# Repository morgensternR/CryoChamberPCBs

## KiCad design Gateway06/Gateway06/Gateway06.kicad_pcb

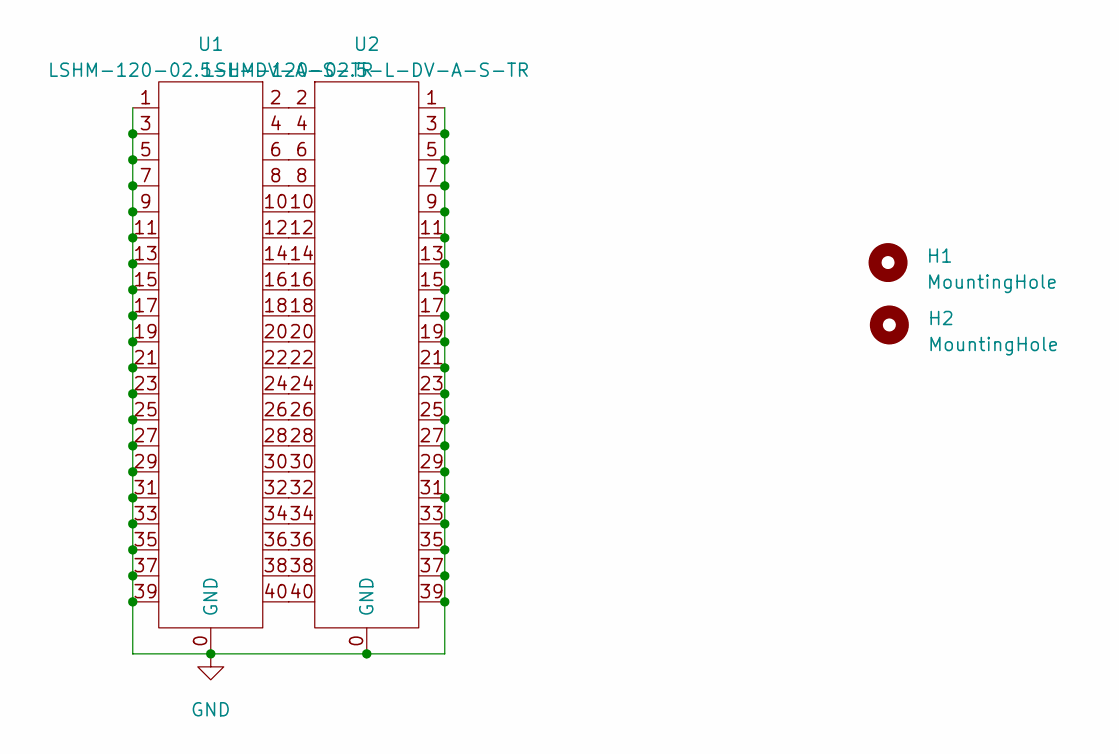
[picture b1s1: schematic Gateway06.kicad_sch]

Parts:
H1, H2: MountingHole; SMA_Hermetic
U1, U2: LSHM-120-02.5-L-DV-A-S-TR

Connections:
GND: U1.0 (GND), U1.1, U1.3, U1.5, U1.7, U1.9, U1.11, U1.13, U1.15, U1.17, U1.19, U1.21, U1.23, U1.25, U1.27, U1.29, U1.31, U1.33, U1.35, U1.37, U1.39, U2.0 (GND), U2.1, U2.3, U2.5, U2.7, U2.9, U2.11, U2.13, U2.15, U2.17, U2.19, U2.21, U2.23, U2.25, U2.27, U2.29, U2.31, U2.33, U2.35, U2.37, U2.39
unnamed: U1.2, U2.2
unnamed: U1.4, U2.4
unnamed: U1.6, U2.6
unnamed: U1.8, U2.8
unnamed: U1.10, U2.10
unnamed: U1.12, U2.12
unnamed: U1.14, U2.14
unnamed: U1.16, U2.16
unnamed: U1.18, U2.18
unnamed: U1.20, U2.20
unnamed: U1.22, U2.22
unnamed: U1.24, U2.24
unnamed: U1.26, U2.26
unnamed: U1.28, U2.28
unnamed: U1.30, U2.30
unnamed: U1.32, U2.32
unnamed: U1.34, U2.34
unnamed: U1.36, U2.36
unnamed: U1.38, U2.38
unnamed: U1.40, U2.40

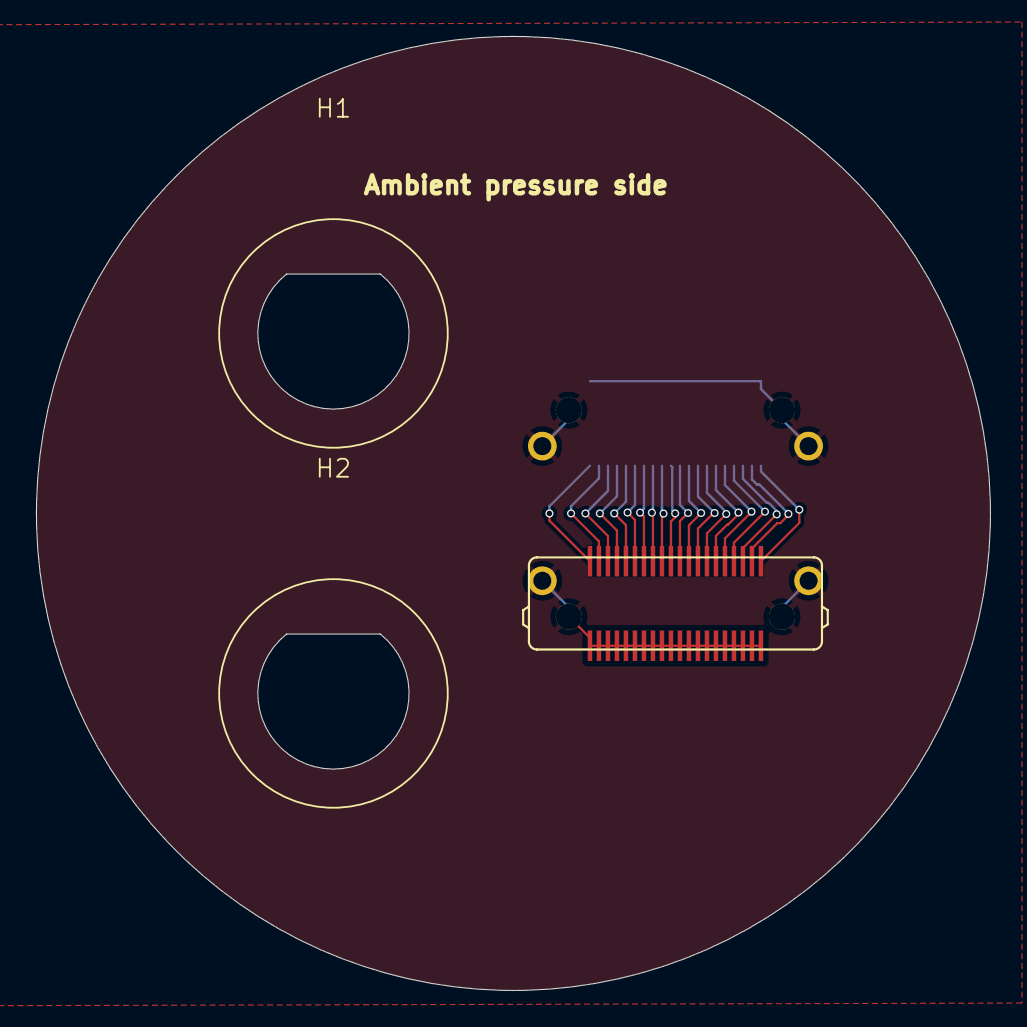
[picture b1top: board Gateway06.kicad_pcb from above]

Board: 2 copper layers, 53.0 x 53.0 mm, 4 parts (1 on the bottom side), 21 nets.

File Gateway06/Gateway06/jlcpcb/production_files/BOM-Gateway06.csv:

Comment,Designator,Footprint,LCSC
MountingHole,H2,SMA_Hermetic,
MountingHole,H1,SMA_Hermetic,
LSHM-120-02.5-L-DV-A-S-TR,U2,LSHM-120-02.5-L-DV-A-S-TR,
LSHM-120-02.5-L-DV-A-S-TR,U1,LSHM-120-02.5-L-DV-A-S-TR,

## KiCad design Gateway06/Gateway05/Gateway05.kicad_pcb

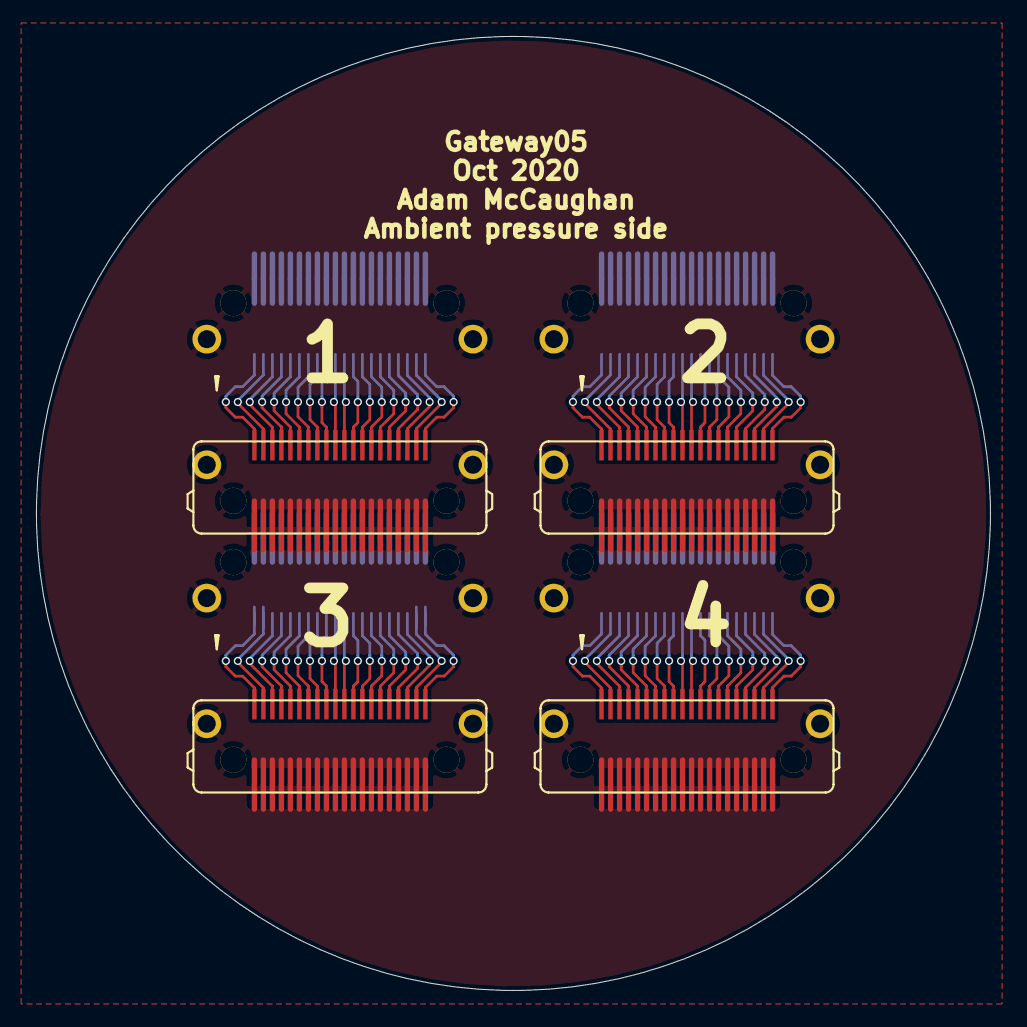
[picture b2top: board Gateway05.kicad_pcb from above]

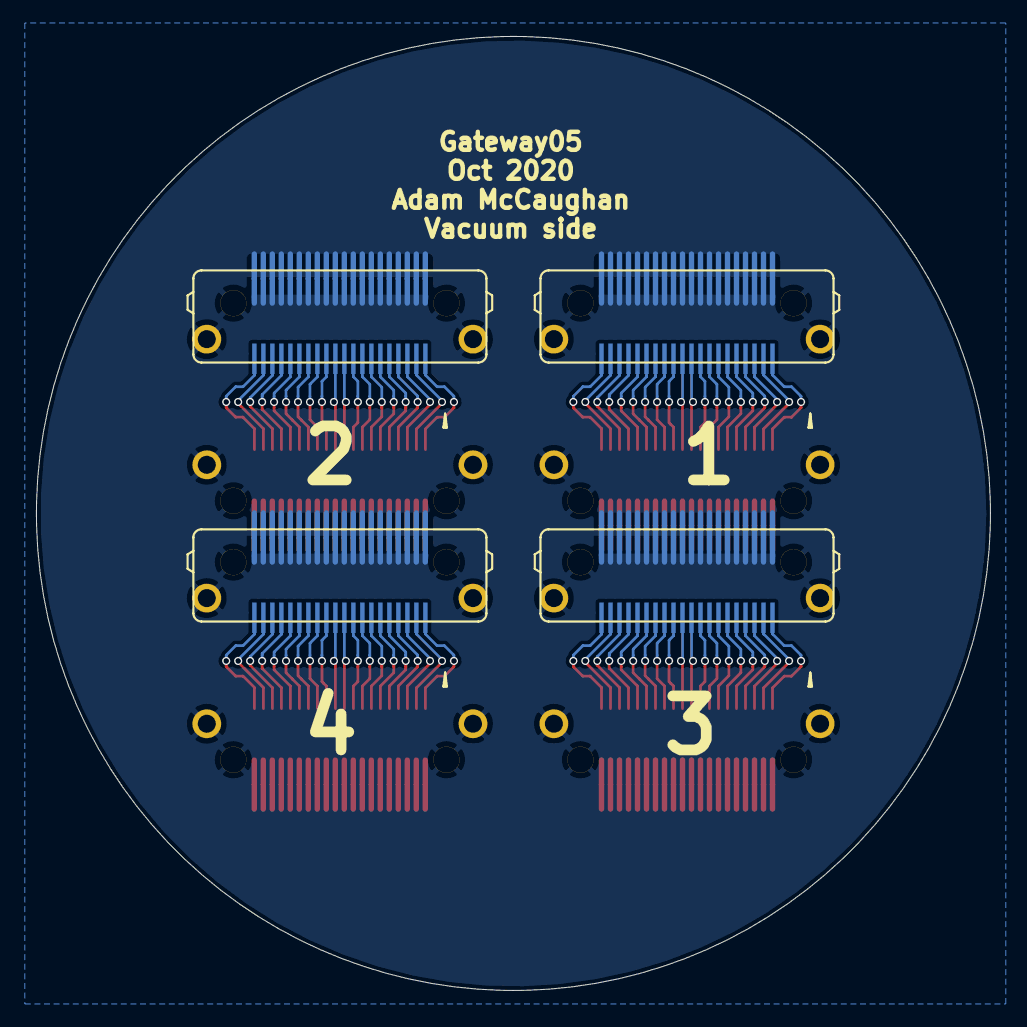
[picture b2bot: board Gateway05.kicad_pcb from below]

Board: 2 copper layers, 53.0 x 53.0 mm, 8 parts (4 on the bottom side), 81 nets.

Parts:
U1, U2, U3, U4, U5, U6, U7, U8: LSHM; LSHM-120-02.5-L-DV-A-S-TR

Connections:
GND: U1.0, U1.1, U1.3, U1.5, U1.7, U1.9, U1.11, U1.13, U1.15, U1.17, U1.19, U1.21, U1.23, U1.25, U1.27, U1.29, U1.31, U1.33, U1.35, U1.37, U1.39, U2.0, U2.1, U2.3, U2.5, U2.7, U2.9, U2.11, U2.13, U2.15, U2.17, U2.19, U2.21, U2.23, U2.25, U2.27, U2.29, U2.31, U2.33, U2.35, U2.37, U2.39, U3.0, U3.1, U3.3, U3.5, U3.7, U3.9, U3.11, U3.13, U3.15, U3.17, U3.19, U3.21, U3.23, U3.25, U3.27, U3.29, U3.31, U3.33, U3.35, U3.37, U3.39, U4.0, U4.1, U4.3, U4.5, U4.7, U4.9, U4.11, U4.13, U4.15, U4.17, U4.19, U4.21, U4.23, U4.25, U4.27, U4.29, U4.31, U4.33, U4.35, U4.37, U4.39, U5.0, U5.1, U5.3, U5.5, U5.7, U5.9, U5.11, U5.13, U5.15, U5.17, U5.19, U5.21, U5.23, U5.25, U5.27, U5.29, U5.31, U5.33, U5.35, U5.37, U5.39, U6.0, U6.1, U6.3, U6.5, U6.7, U6.9, U6.11, U6.13, U6.15, U6.17, U6.19, U6.21, U6.23, U6.25, U6.27, U6.29, U6.31, U6.33, U6.35, U6.37, U6.39, U7.0, U7.1, U7.3, U7.5, U7.7, U7.9, U7.11, U7.13, U7.15, U7.17, U7.19, U7.21, U7.23, U7.25, U7.27, U7.29, U7.31, U7.33, U7.35, U7.37, U7.39, U8.0, U8.1, U8.3, U8.5, U8.7, U8.9, U8.11, U8.13, U8.15, U8.17, U8.19, U8.21, U8.23, U8.25, U8.27, U8.29, U8.31, U8.33, U8.35, U8.37, U8.39
unnamed: U1.2, U2.2
unnamed: U1.4, U2.4
unnamed: U1.6, U2.6
unnamed: U1.8, U2.8
unnamed: U1.10, U2.10
unnamed: U1.12, U2.12
unnamed: U1.14, U2.14
unnamed: U1.16, U2.16
unnamed: U1.18, U2.18
unnamed: U1.20, U2.20
unnamed: U1.22, U2.22
unnamed: U1.24, U2.24
unnamed: U1.26, U2.26
unnamed: U1.28, U2.28
unnamed: U1.30, U2.30
unnamed: U1.32, U2.32
unnamed: U1.34, U2.34
unnamed: U1.36, U2.36
unnamed: U1.38, U2.38
unnamed: U1.40, U2.40
unnamed: U3.2, U4.2
unnamed: U3.4, U4.4
unnamed: U3.6, U4.6
unnamed: U3.8, U4.8
unnamed: U3.10, U4.10
unnamed: U3.12, U4.12
unnamed: U3.14, U4.14
unnamed: U3.16, U4.16
unnamed: U3.18, U4.18
unnamed: U3.20, U4.20
unnamed: U3.22, U4.22
unnamed: U3.24, U4.24
unnamed: U3.26, U4.26
unnamed: U3.28, U4.28
unnamed: U3.30, U4.30
unnamed: U3.32, U4.32
unnamed: U3.34, U4.34
unnamed: U3.36, U4.36
unnamed: U3.38, U4.38
unnamed: U3.40, U4.40
unnamed: U5.2, U6.2
unnamed: U5.4, U6.4
unnamed: U5.6, U6.6
unnamed: U5.8, U6.8
unnamed: U5.10, U6.10
unnamed: U5.12, U6.12
unnamed: U5.14, U6.14
unnamed: U5.16, U6.16
unnamed: U5.18, U6.18
unnamed: U5.20, U6.20
unnamed: U5.22, U6.22
unnamed: U5.24, U6.24
unnamed: U5.26, U6.26
unnamed: U5.28, U6.28
unnamed: U5.30, U6.30
unnamed: U5.32, U6.32
unnamed: U5.34, U6.34
unnamed: U5.36, U6.36
unnamed: U5.38, U6.38
unnamed: U5.40, U6.40
unnamed: U7.2, U8.2
unnamed: U7.4, U8.4
unnamed: U7.6, U8.6
unnamed: U7.8, U8.8
unnamed: U7.10, U8.10
unnamed: U7.12, U8.12
unnamed: U7.14, U8.14
unnamed: U7.16, U8.16
unnamed: U7.18, U8.18
unnamed: U7.20, U8.20
unnamed: U7.22, U8.22
unnamed: U7.24, U8.24
unnamed: U7.26, U8.26
unnamed: U7.28, U8.28
unnamed: U7.30, U8.30
unnamed: U7.32, U8.32
unnamed: U7.34, U8.34
unnamed: U7.36, U8.36
unnamed: U7.38, U8.38
unnamed: U7.40, U8.40

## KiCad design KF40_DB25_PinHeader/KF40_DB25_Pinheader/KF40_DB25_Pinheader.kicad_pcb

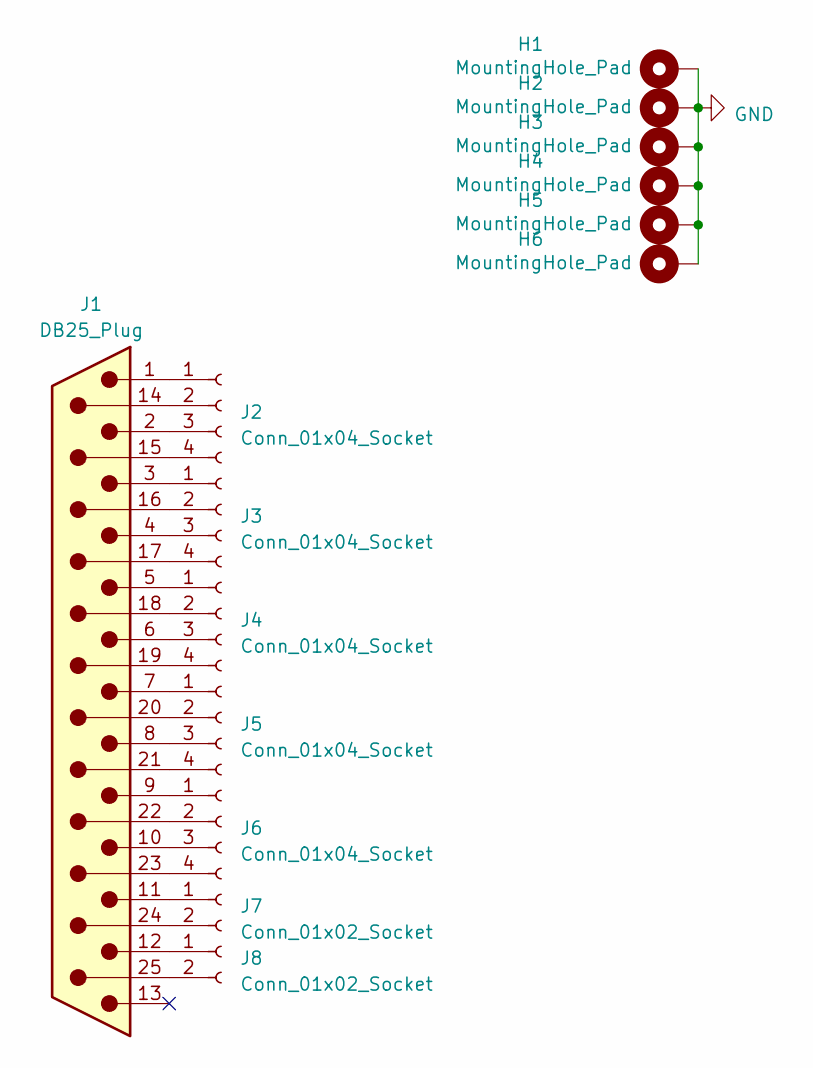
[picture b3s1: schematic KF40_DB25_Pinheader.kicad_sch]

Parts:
H1, H2, H3, H4, H5, H6: MountingHole_Pad; MountingHole_5mm_Pad
J1: DB25_Plug; DB25-TH_FDB2501-M0DB300K6KA; LCSC C2834344
J2, J3, J4, J5, J6: Conn_01x04_Socket; PinSocket_1x04_P2.54mm_Vertical; LCSC C2718488
J7, J8: Conn_01x02_Socket; PinSocket_1x02_P2.54mm_Vertical; LCSC C2935896

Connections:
GND: H1.1, H2.1, H3.1, H4.1, H5.1, H6.1
unnamed: J1.14, J2.2
unnamed: J1.15, J2.4
unnamed: J1.16, J3.2
unnamed: J1.17, J3.4
unnamed: J1.18, J4.2
unnamed: J1.19, J4.4
unnamed: J1.20, J5.2
unnamed: J1.21, J5.4
unnamed: J1.22, J6.2
unnamed: J1.23, J6.4
unnamed: J1.24, J7.2
unnamed: J1.25, J8.2
unnamed: J1.1, J2.1
unnamed: J1.2, J2.3
unnamed: J1.3, J3.1
unnamed: J1.4, J3.3
unnamed: J1.5, J4.1
unnamed: J1.6, J4.3
unnamed: J1.7, J5.1
unnamed: J1.8, J5.3
unnamed: J1.9, J6.1
unnamed: J1.10, J6.3
unnamed: J1.11, J7.1
unnamed: J1.12, J8.1

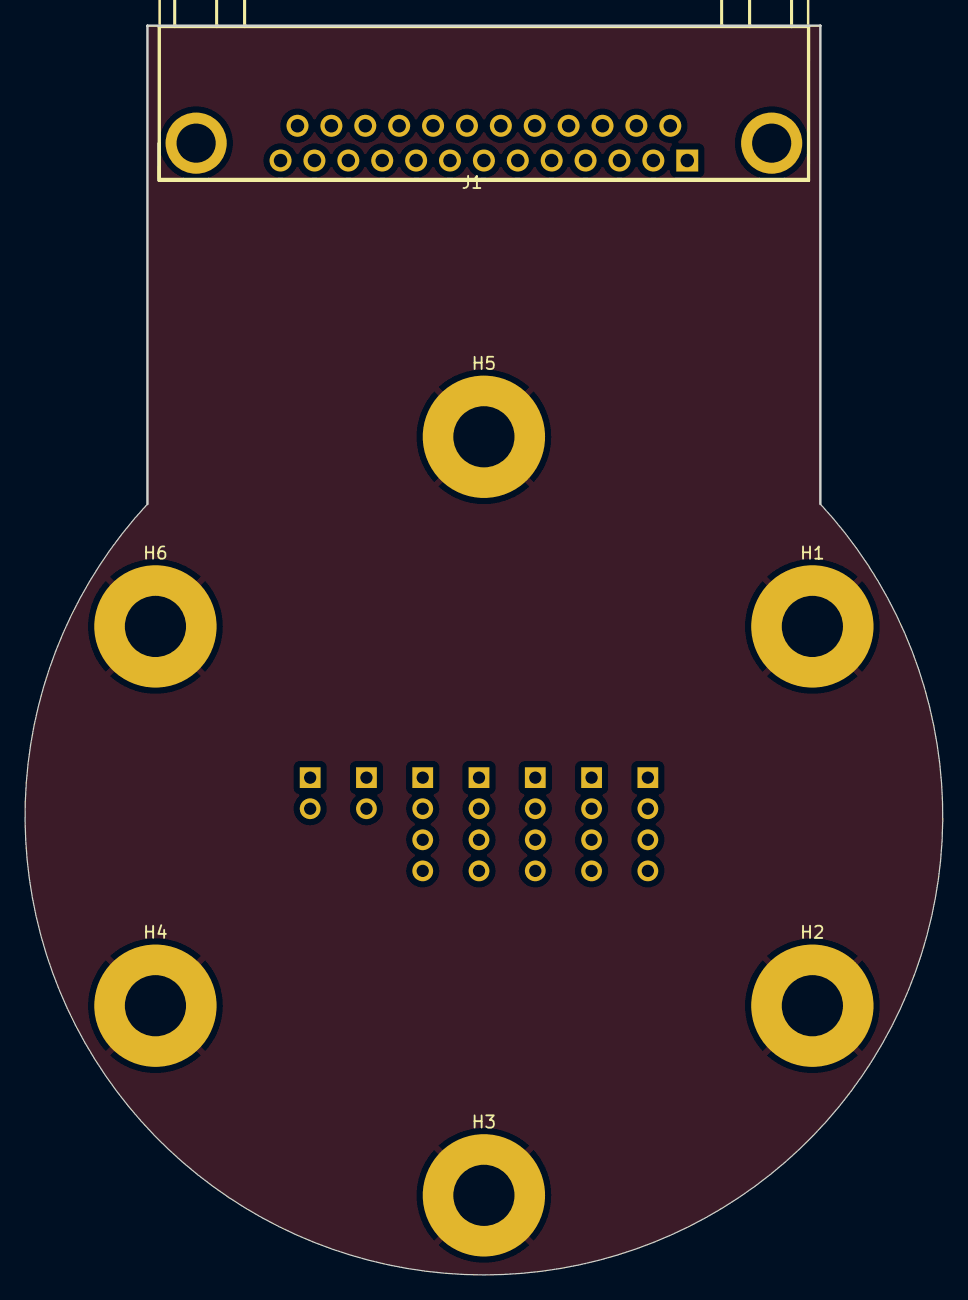
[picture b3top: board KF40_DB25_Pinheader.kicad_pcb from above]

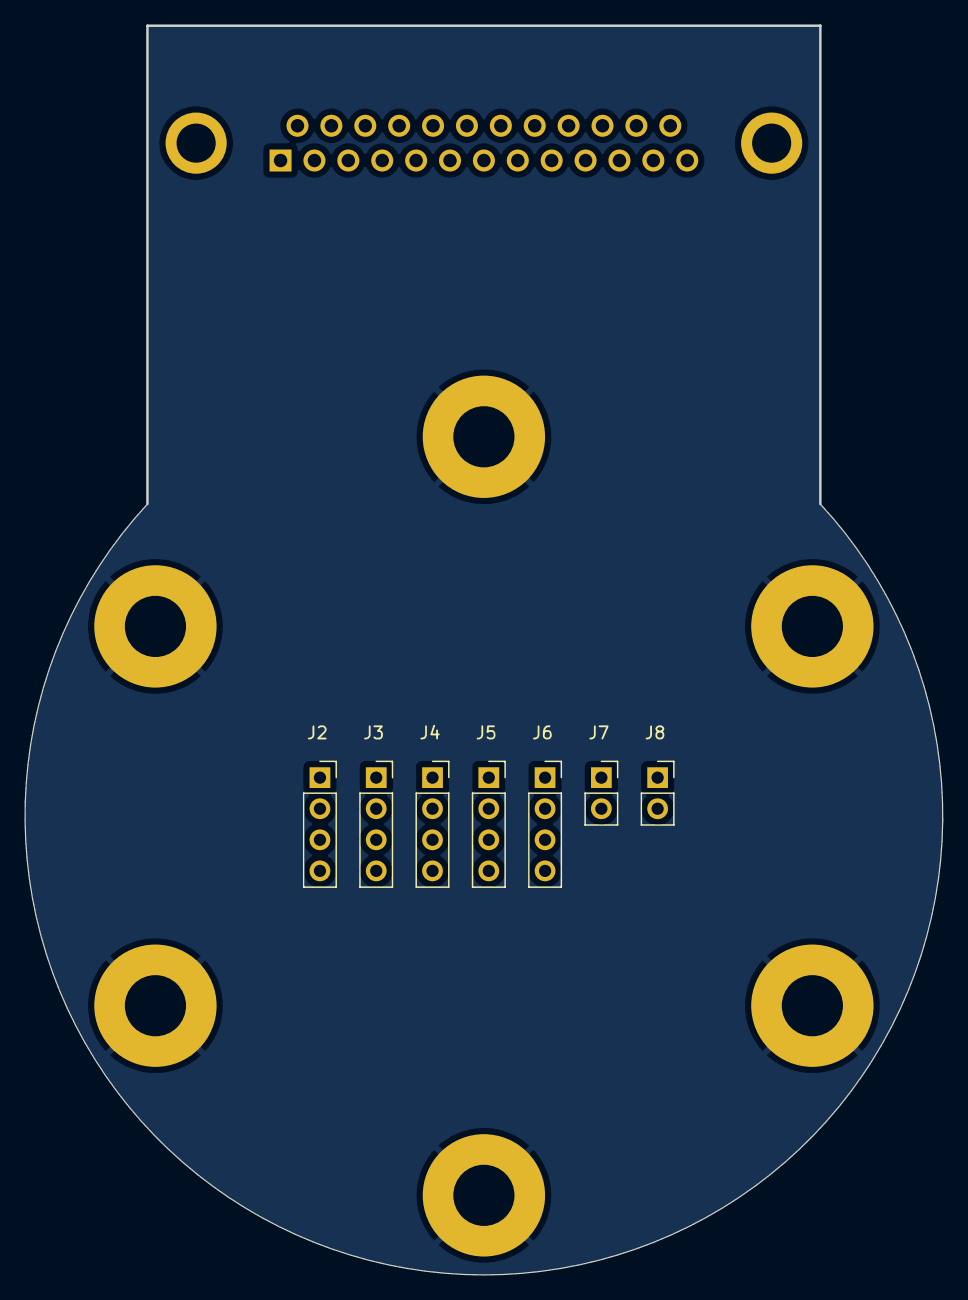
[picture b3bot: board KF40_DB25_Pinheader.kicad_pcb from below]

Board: 4 copper layers, 75.0 x 102.1 mm, 14 parts (7 on the bottom side), 25 nets.

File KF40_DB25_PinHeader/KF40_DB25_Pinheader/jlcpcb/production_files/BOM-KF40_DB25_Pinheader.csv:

Comment,Designator,Footprint,LCSC
Conn_01x04_Socket,"J2,J3,J4,J5,J6",PinSocket_1x04_P2.54mm_Vertical,C2718488
DB25_Plug,J1,DB25-TH_FDB2501-M0DB300K6KA,C2834344
Conn_01x02_Socket,"J7,J8",PinSocket_1x02_P2.54mm_Vertical,C2935896
MountingHole_Pad,H2,MountingHole_5mm_Pad,
MountingHole_Pad,H6,MountingHole_5mm_Pad,
MountingHole_Pad,H4,MountingHole_5mm_Pad,
MountingHole_Pad,H1,MountingHole_5mm_Pad,
MountingHole_Pad,H5,MountingHole_5mm_Pad,
MountingHole_Pad,H3,MountingHole_5mm_Pad,

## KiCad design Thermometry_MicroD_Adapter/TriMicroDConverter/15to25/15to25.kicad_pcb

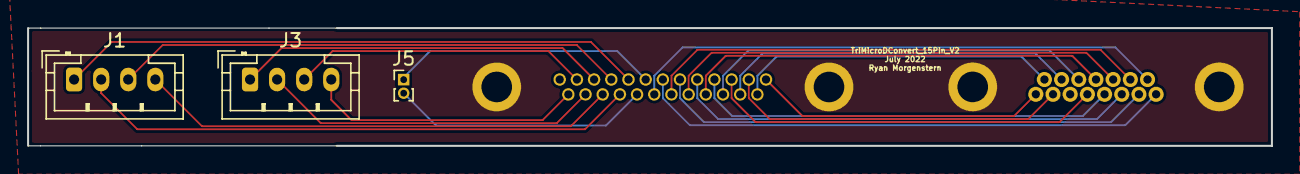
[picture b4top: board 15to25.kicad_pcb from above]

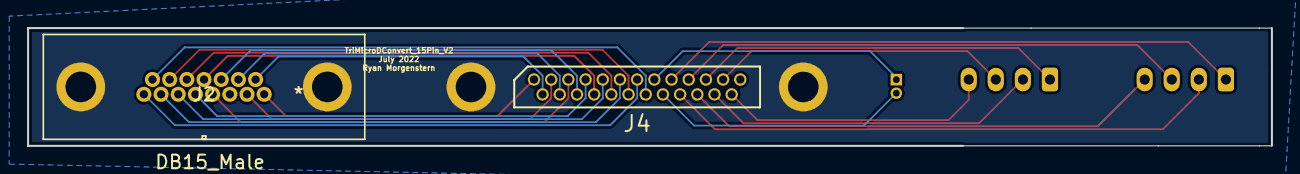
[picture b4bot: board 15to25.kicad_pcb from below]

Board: 2 copper layers, 91.9 x 8.7 mm, 5 parts (2 on the bottom side), 25 nets.

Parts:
J1, J3: Conn_01x04; JST_PH_B4B-PH-K_1x04_P2.00mm_Vertical
J2: DB15_Male; 380-015-113L001
J4: DB25_Male; Norcomp-380-025-113L001-microd_NoLeads
J5: Conn_01x02; PinHeader_1x02_P1.00mm_Vertical

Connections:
GND: J2.0, J4.0
unnamed: J1.1, J4.9
unnamed: J1.2, J4.22
unnamed: J1.3, J4.10
unnamed: J1.4, J4.23
unnamed: J2.1, J4.1
unnamed: J2.2, J4.2
unnamed: J2.4, J4.3
unnamed: J2.5, J4.4
unnamed: J2.6, J4.5
unnamed: J2.7, J4.6
unnamed: J2.8, J4.7
unnamed: J2.9, J4.14
unnamed: J2.10, J4.15
unnamed: J2.11, J4.16
unnamed: J2.12, J4.17
unnamed: J2.13, J4.18
unnamed: J2.14, J4.19
unnamed: J2.15, J4.20
unnamed: J3.1, J4.11
unnamed: J3.2, J4.24
unnamed: J3.3, J4.12
unnamed: J3.4, J4.25
unnamed: J4.8, J5.1
unnamed: J4.21, J5.2

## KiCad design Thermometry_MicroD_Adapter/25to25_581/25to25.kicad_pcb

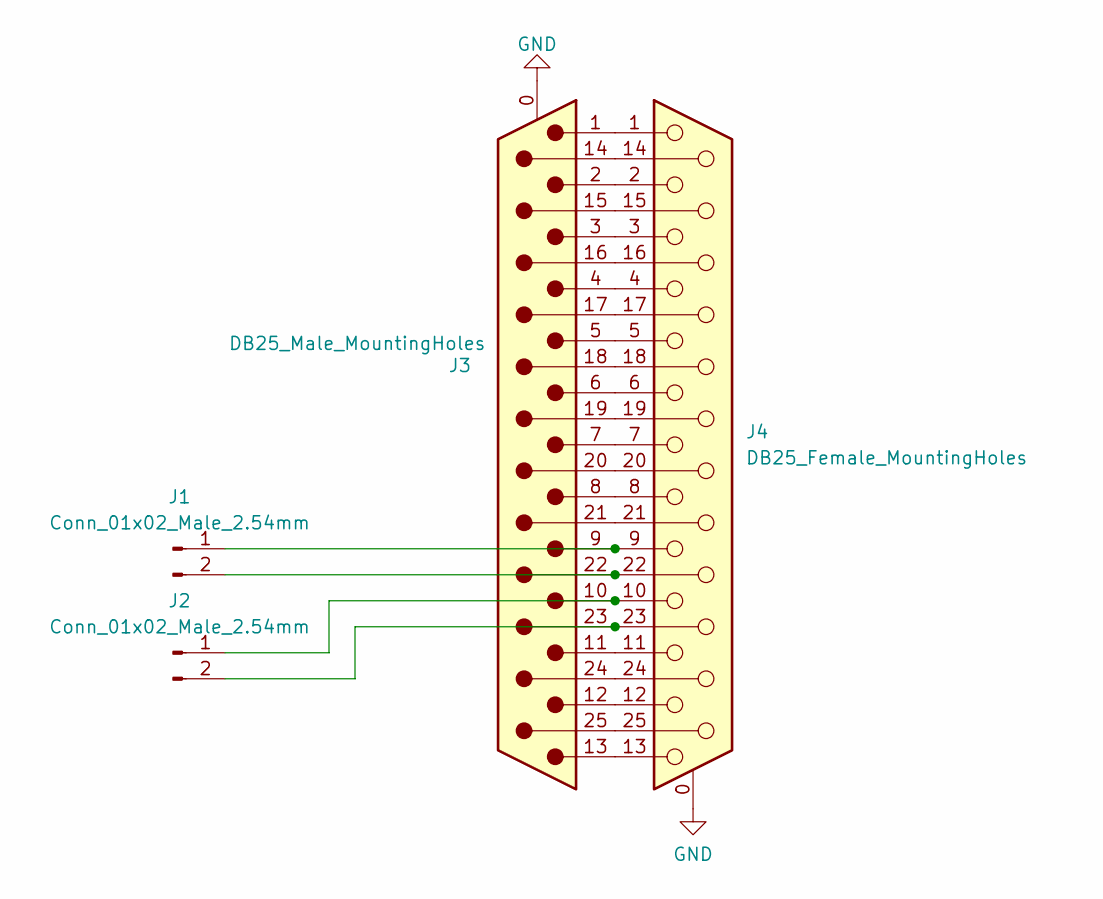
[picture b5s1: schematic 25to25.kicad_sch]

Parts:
J1, J2: Conn_01x02_Male_2.54mm; PinHeader_1x02_P2.54mm_Horizontal; MPN PZ254V-11-02P; LCSC C492401
J3: DB25_Male_MountingHoles; 581M25113L461_Norcomp
J4: DB25_Female_MountingHoles; 581M25213L461_Norcomp_Female

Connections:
GND: J3.0 (PAD), J4.0 (PAD)
unnamed: J1.1, J3.9, J4.9
unnamed: J1.2, J3.22, J4.22
unnamed: J2.1, J3.10, J4.10
unnamed: J2.2, J3.23, J4.23
unnamed: J3.1, J4.1
unnamed: J3.2, J4.2
unnamed: J3.3, J4.3
unnamed: J3.4, J4.4
unnamed: J3.5, J4.5
unnamed: J3.6, J4.6
unnamed: J3.7, J4.7
unnamed: J3.8, J4.8
unnamed: J3.11, J4.11
unnamed: J3.12, J4.12
unnamed: J3.13, J4.13
unnamed: J3.14, J4.14
unnamed: J3.15, J4.15
unnamed: J3.16, J4.16
unnamed: J3.17, J4.17
unnamed: J3.18, J4.18
unnamed: J3.19, J4.19
unnamed: J3.20, J4.20
unnamed: J3.21, J4.21
unnamed: J3.24, J4.24
unnamed: J3.25, J4.25

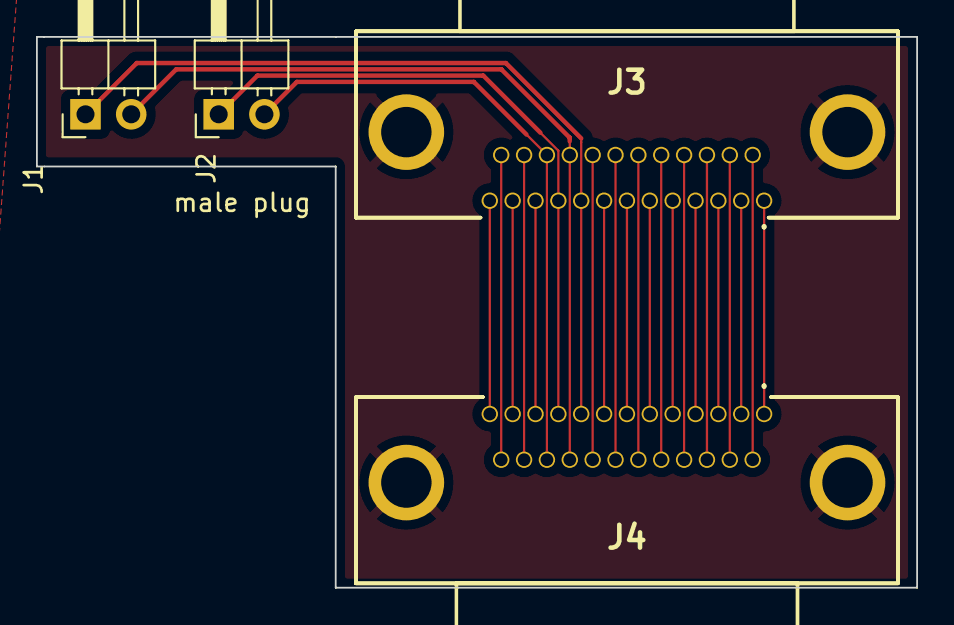
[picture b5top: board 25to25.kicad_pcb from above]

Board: 2 copper layers, 48.9 x 30.6 mm, 4 parts (0 on the bottom side), 26 nets.

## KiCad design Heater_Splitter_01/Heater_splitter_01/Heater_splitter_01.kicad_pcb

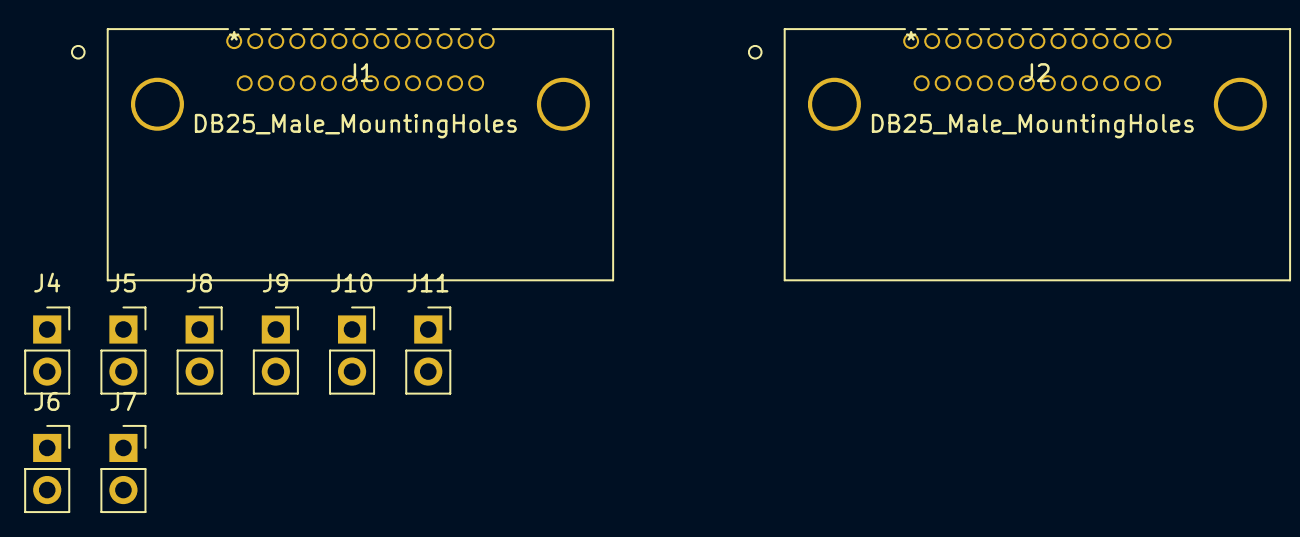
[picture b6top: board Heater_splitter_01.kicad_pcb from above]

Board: 2 copper layers, 10 parts (0 on the bottom side), 24 nets, no tracks yet.

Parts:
J1, J2: DB25_Male_MountingHoles; 381-025-112L565
J4, J5, J6, J7, J8, J9, J10, J11: Conn_01x02; PinSocket_1x02_P2.54mm_Vertical

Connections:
/9: J1.9, J2.9, J4.1, J5.1, J6.1, J7.1
/10: J1.10, J2.10, J8.1, J9.1, J10.1, J11.1
/22: J1.22, J2.22, J4.2, J5.2, J6.2, J7.2
/23: J1.23, J2.23, J8.2, J9.2, J10.2, J11.2
GND: J1.0, J2.0
unnamed: J1.1, J2.1
unnamed: J1.2, J2.2
unnamed: J1.4, J2.4
unnamed: J1.5, J2.5
unnamed: J1.6, J2.6
unnamed: J1.7, J2.7
unnamed: J1.8, J2.8
unnamed: J1.11, J2.11
unnamed: J1.12, J2.12
unnamed: J1.14, J2.14
unnamed: J1.15, J2.15
unnamed: J1.16, J2.16
unnamed: J1.17, J2.17
unnamed: J1.18, J2.18
unnamed: J1.19, J2.19
unnamed: J1.20, J2.20
unnamed: J1.21, J2.21
unnamed: J1.24, J2.24
unnamed: J1.25, J2.25

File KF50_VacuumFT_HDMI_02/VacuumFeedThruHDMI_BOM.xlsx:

Comment | Designator | Footprint | LCSC
HDMI | J1 J2 J3 J4 J5 J6 J7 J8 J9 | Connector:HDMI-Vertical-Male-JLBPCB | C168715

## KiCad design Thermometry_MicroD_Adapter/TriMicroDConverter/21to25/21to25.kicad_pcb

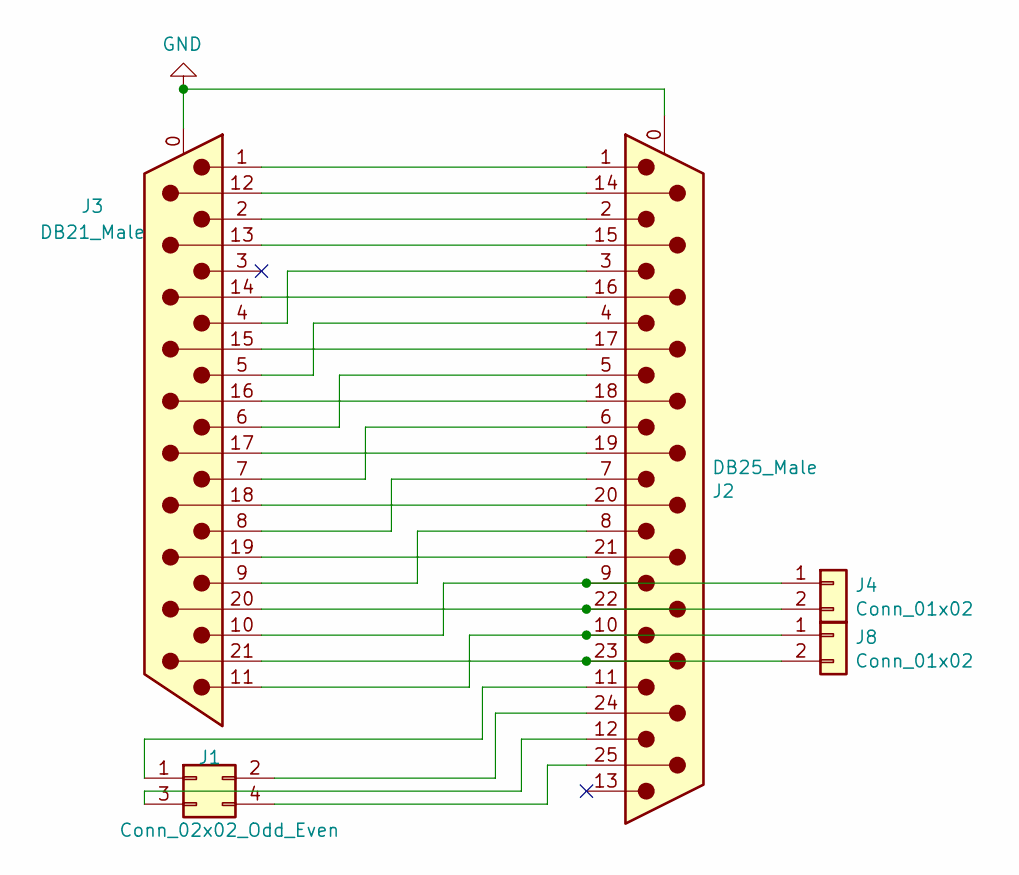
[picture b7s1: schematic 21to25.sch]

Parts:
J1: Conn_02x02_Odd_Even; PinHeader_2x02_P1.00mm_Vertical
J2: DB25_Male; Norcomp-380-025-113L001-microd_NoLeads
J3: DB21_Male; Omnetics_21Pin
J4, J8: Conn_01x02; PinSocket_1x02_P2.54mm_Vertical; LCSC C225188

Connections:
GND: J2.0 (PAD), J3.0
unnamed: J1.1, J2.11
unnamed: J1.2, J2.24
unnamed: J1.3, J2.12
unnamed: J1.4, J2.25
unnamed: J2.1, J3.1
unnamed: J2.2, J3.2
unnamed: J2.3, J3.4
unnamed: J2.4, J3.5
unnamed: J2.5, J3.6
unnamed: J2.6, J3.7
unnamed: J2.7, J3.8
unnamed: J2.8, J3.9
unnamed: J2.9, J3.10, J4.1
unnamed: J2.10, J3.11, J8.1
unnamed: J2.14, J3.12
unnamed: J2.15, J3.13
unnamed: J2.16, J3.14
unnamed: J2.17, J3.15
unnamed: J2.18, J3.16
unnamed: J2.19, J3.17
unnamed: J2.20, J3.18
unnamed: J2.21, J3.19
unnamed: J2.22, J3.20, J4.2
unnamed: J2.23, J3.21, J8.2

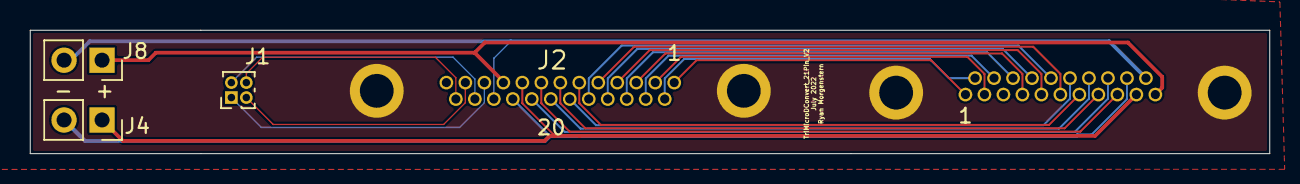
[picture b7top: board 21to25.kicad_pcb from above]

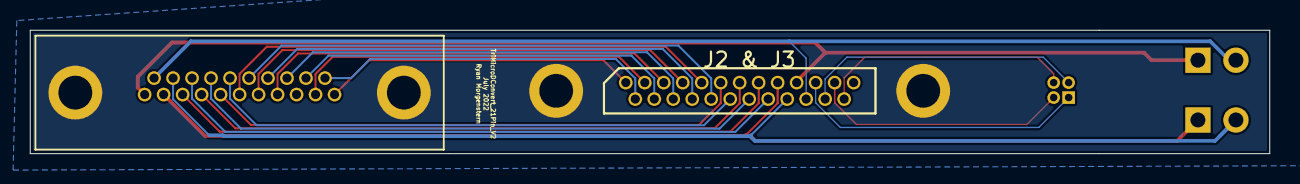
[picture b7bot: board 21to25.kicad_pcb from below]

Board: 2 copper layers, 82.9 x 8.2 mm, 5 parts (2 on the bottom side), 25 nets.

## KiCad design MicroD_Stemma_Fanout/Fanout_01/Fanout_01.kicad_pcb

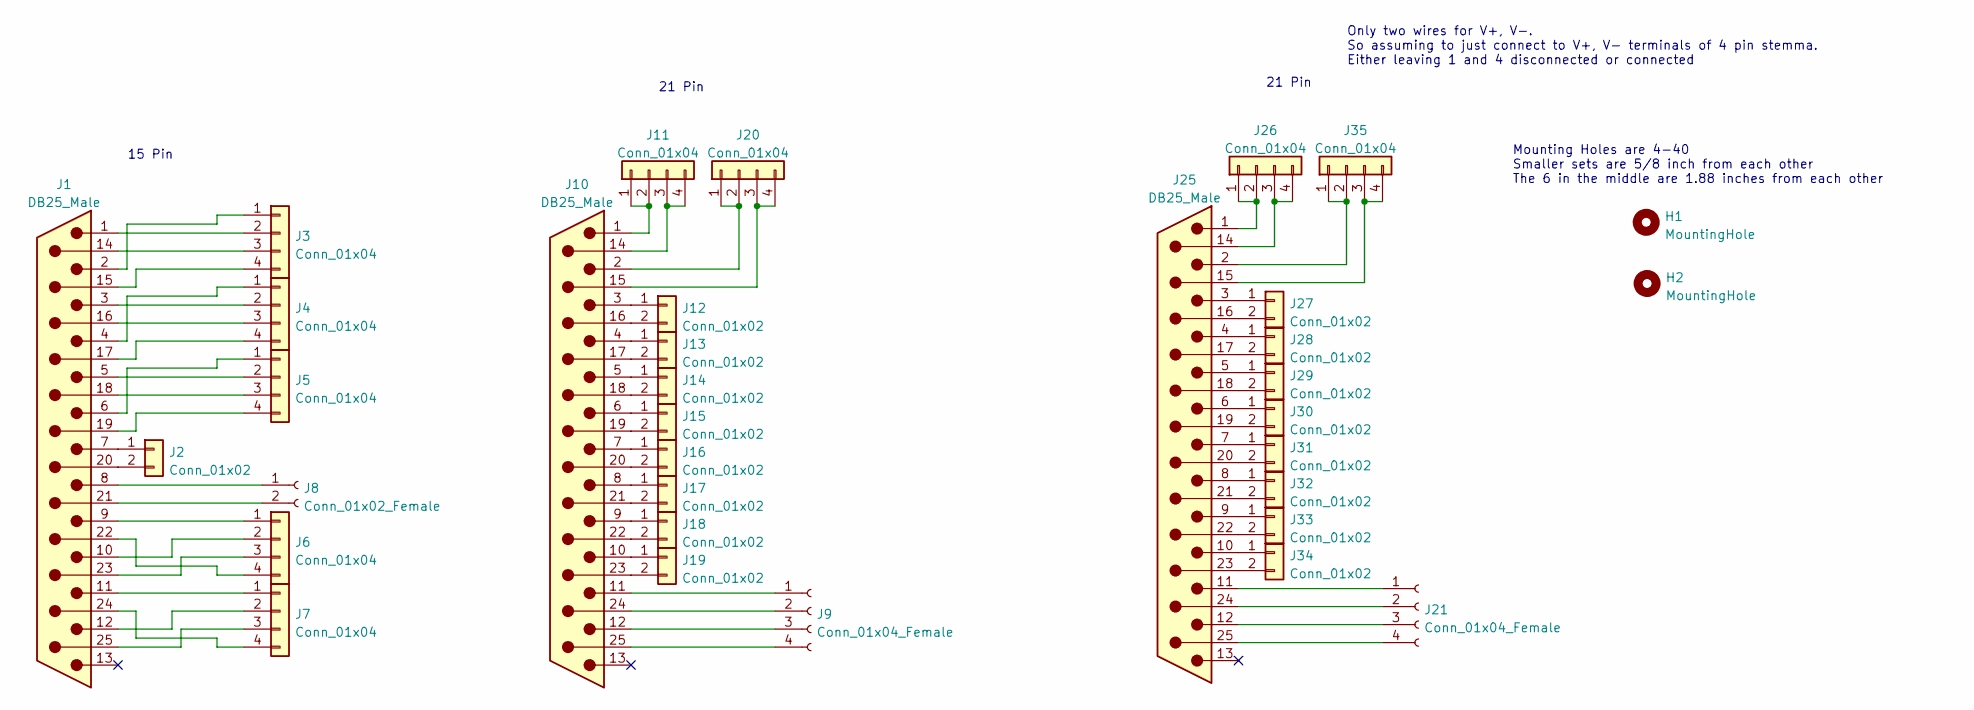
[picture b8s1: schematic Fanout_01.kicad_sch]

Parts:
H1, H2: MountingHole; MountingHole_3.5mm
J1, J10, J25: DB25_Male; NORCOMP_380-025-113L001
J2, J12, J13, J14, J15, J16, J17, J18, J19, J27, J28, J29, J30, J31, J32, J33, J34: Conn_01x02; JST_PH_S2B-PH-K_1x02_P2.00mm_Horizontal; LCSC C16965
J3, J4, J5, J6, J7, J11, J20, J26, J35: Conn_01x04; JST_SH_SM04B-SRSS-TB_1x04-1MP_P1.00mm_Horizontal; LCSC C371571
J8: Conn_01x02_Female; PinSocket_1x02_P2.54mm_Vertical
J9, J21: Conn_01x04_Female; PinSocket_1x04_P2.54mm_Vertical

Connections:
unnamed: J1.1, J3.2
unnamed: J1.2, J3.1
unnamed: J1.3, J4.2
unnamed: J1.4, J4.1
unnamed: J1.5, J5.2
unnamed: J1.6, J5.1
unnamed: J1.7, J2.1
unnamed: J1.8, J8.1
unnamed: J1.9, J6.1
unnamed: J1.10, J6.2
unnamed: J1.11, J7.1
unnamed: J1.12, J7.2
unnamed: J1.14, J3.3
unnamed: J1.15, J3.4
unnamed: J1.16, J4.3
unnamed: J1.17, J4.4
unnamed: J1.18, J5.3
unnamed: J1.19, J5.4
unnamed: J1.20, J2.2
unnamed: J1.21, J8.2
unnamed: J1.22, J6.4
unnamed: J1.23, J6.3
unnamed: J1.24, J7.4
unnamed: J1.25, J7.3
unnamed: J10.1, J11.1, J11.2
unnamed: J10.2, J20.1, J20.2
unnamed: J10.3, J12.1
unnamed: J10.4, J13.1
unnamed: J10.5, J14.1
unnamed: J10.6, J15.1
unnamed: J10.7, J16.1
unnamed: J10.8, J17.1
unnamed: J10.9, J18.1
unnamed: J10.10, J19.1
unnamed: J9.1, J10.11
unnamed: J9.3, J10.12
unnamed: J10.14, J11.3, J11.4
unnamed: J10.15, J20.3, J20.4
unnamed: J10.16, J12.2
unnamed: J10.17, J13.2
unnamed: J10.18, J14.2
unnamed: J10.19, J15.2
unnamed: J10.20, J16.2
unnamed: J10.21, J17.2
unnamed: J10.22, J18.2
unnamed: J10.23, J19.2
unnamed: J9.2, J10.24
unnamed: J9.4, J10.25
unnamed: J25.1, J26.1, J26.2
unnamed: J25.2, J35.1, J35.2
unnamed: J25.3, J27.1
unnamed: J25.4, J28.1
unnamed: J25.5, J29.1
unnamed: J25.6, J30.1
unnamed: J25.7, J31.1
unnamed: J25.8, J32.1
unnamed: J25.9, J33.1
unnamed: J25.10, J34.1
unnamed: J21.1, J25.11
unnamed: J21.3, J25.12
unnamed: J25.14, J26.3, J26.4
unnamed: J25.15, J35.3, J35.4
unnamed: J25.16, J27.2
unnamed: J25.17, J28.2
unnamed: J25.18, J29.2
unnamed: J25.19, J30.2
unnamed: J25.20, J31.2
unnamed: J25.21, J32.2
unnamed: J25.22, J33.2
unnamed: J25.23, J34.2
unnamed: J21.2, J25.24
unnamed: J21.4, J25.25

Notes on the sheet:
Only two wires for V+, V-. So assuming to just connect to V+, V- terminals of 4 pin stemma. Either leaving 1 and 4 disconnected or connected
15 Pin
21 Pin
Mounting Holes are 4-40 Smaller sets are 5/8 inch from each other The 6 in the middle are 1.88 inches from each other

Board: 2 copper layers, 34 parts (3 on the bottom side), 72 nets, no tracks yet.

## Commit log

2021-08-04 Initial Push
2021-08-06 Main Commit
2021-08-06 ReUpdate
2021-08-07 Update Gerber
2021-08-09 Updated
    4 Pair in HDMI
    Fixed Gnds
2021-08-09 Update
    Moved +/- pairs on top of each other
2021-08-09 HDMI Support
2021-08-10 Updated ThermoAdapter
    Overlayed +/- traces
2021-08-10 Updated Gerber
2021-08-11 Update Annotations and Surface Mounts
2022-01-13 HDMI_FT_02 Addition
2022-01-20 Added Db9 to hdmi
2022-02-09 Updated Heater Traces
2022-02-10 Fixed
2022-03-08 Update oring and removed microD holes
2022-04-08 Fixed Trace to hole spacing
2022-06-04 Added MicroD to Stemma
2022-07-14 Update
    Added current versions of adapter boards.
    Added heater line splitter
2022-07-15 update
    fixed 581
2022-08-10 Fixed Error in board. Added diagrams
2023-12-18 gateway
2023-12-18 update pinout

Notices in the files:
parts and their libraries:
Copyright 2021 Accelerated Designs. All rights reserved.
